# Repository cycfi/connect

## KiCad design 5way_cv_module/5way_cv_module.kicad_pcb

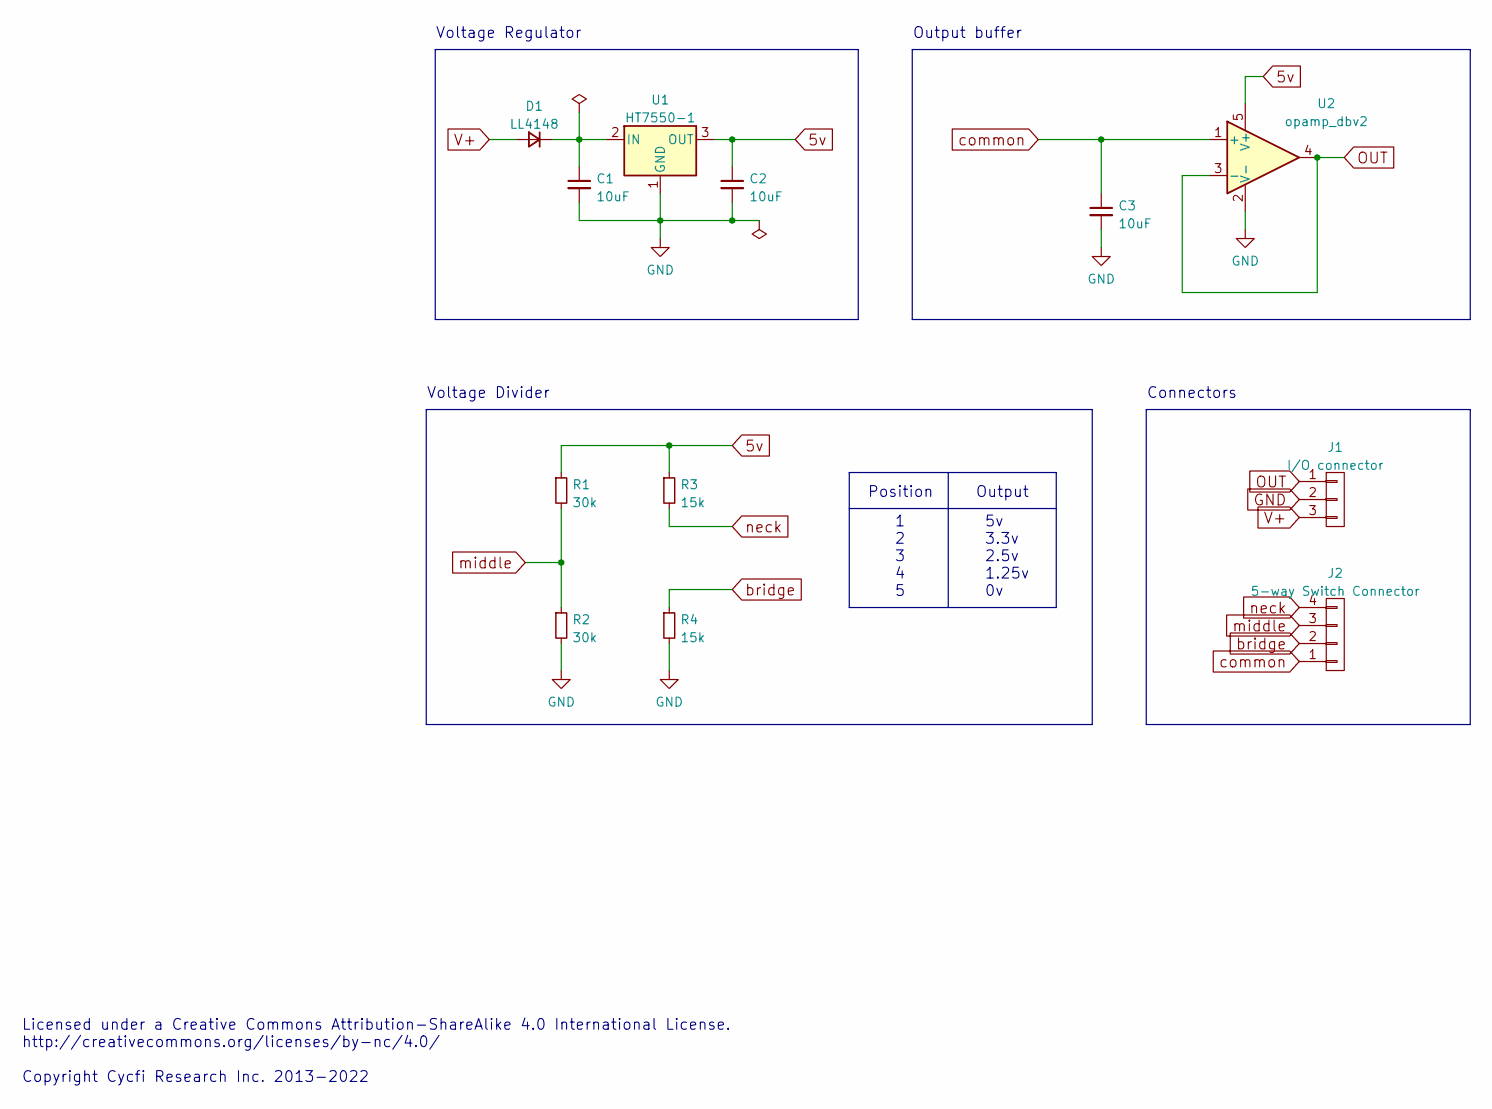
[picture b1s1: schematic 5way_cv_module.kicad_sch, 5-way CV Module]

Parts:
C1, C2, C3: 10uF; C_0603_1608Metric
D1: LL4148; D_MiniMELF
J1: I/O connector; pin_header_1x3p_2.54mm_smd_horizontal
J2: 5-way Switch Connector; pin_socket_1x4p_2.54mm_smd_horizontal
R1, R2: 30k; R_0402_1005Metric
R3, R4: 15k; R_0402_1005Metric
U1: HT7550-1; SOT-89-3
U2: opamp_dbv2; SOT-23-5

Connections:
5v: C2.1, R1.1, R3.1, U1.3 (OUT), U2.5 (V+)
GND: C1.2, C2.2, C3.2, J1.2, R2.2, R4.2, U1.1 (GND), U2.2 (V-)
unnamed: C1.1, D1.1 (K), U1.2 (IN)
OUT: J1.1, U2.3 (-), U2.4
V+: D1.2 (A), J1.3
bridge: J2.2, R4.1
common: C3.1, J2.1, U2.1 (+)
middle: J2.3, R1.2, R2.1
neck: J2.4, R3.2

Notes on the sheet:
Output
5v 3.3v 2.5v 1.25v 0v
Connectors
Voltage Divider
1 2 3 4 5
Licensed under a Creative Commons Attribution-ShareAlike 4.0 International License. http://creativecommons.org/licenses/by-nc/4.0/ Copyright Cycfi Research Inc. 2013-2022
Output buffer
Voltage Regulator
Position

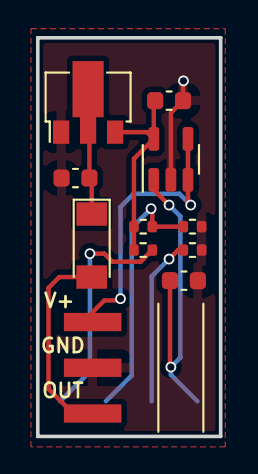
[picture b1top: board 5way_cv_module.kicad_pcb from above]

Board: 2 copper layers, 10.2 x 22.1 mm, 12 parts (1 on the bottom side), 9 nets.

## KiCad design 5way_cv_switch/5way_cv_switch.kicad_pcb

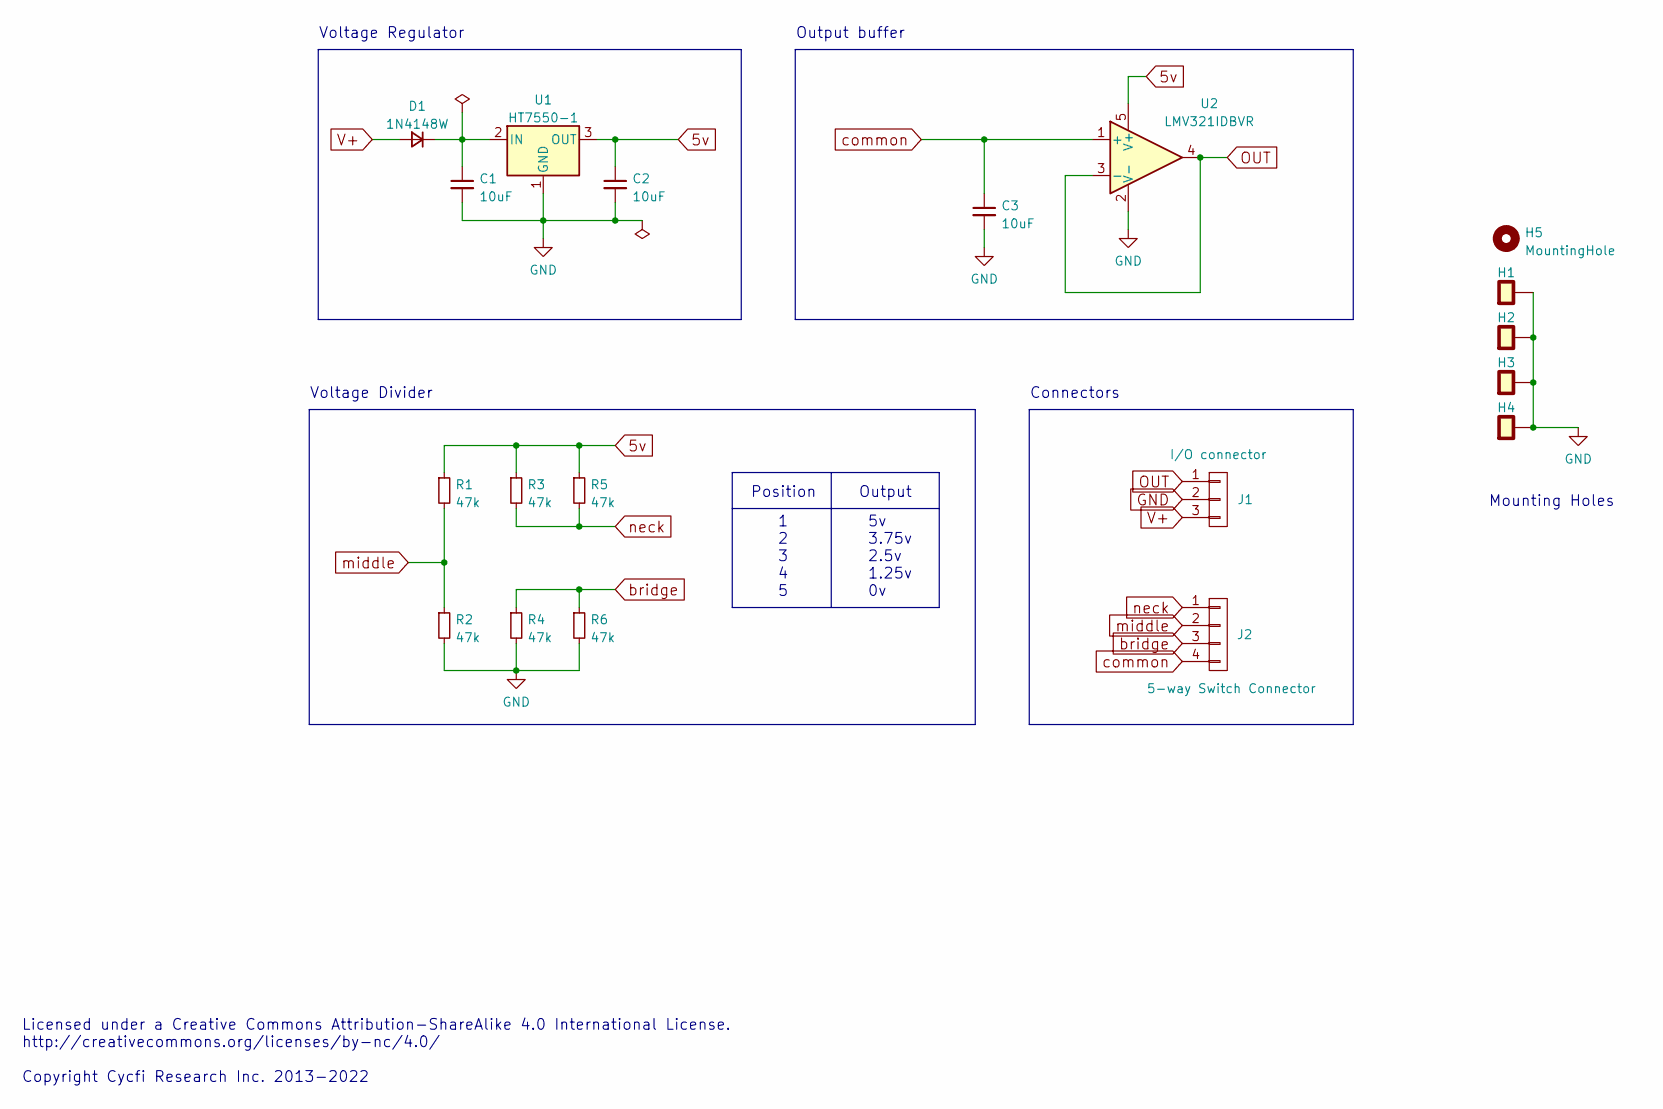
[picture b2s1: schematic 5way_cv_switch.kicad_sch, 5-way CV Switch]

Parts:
C1, C2, C3: 10uF; C_0805_2012Metric; LCSC C15850
D1: 1N4148W; D_SOD-123; LCSC C81598
H1, H2, H3, H4: single_pad; cond_hole_rect_1.2x3.5mm
H5: MountingHole; hole_2.65mm
J1: I/O connector; pin_header_1x3p_2.54mm_smd_horizontal
J2: 5-way Switch Connector; 5way_switch
R1, R2, R3, R4, R5, R6: 47k; R_0402_1005Metric; LCSC C25792
U1: HT7550-1; SOT-89-3; LCSC C16106
U2: LMV321IDBVR; SOT-23-5; LCSC C7972

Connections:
5v: C2.1, R1.1, R3.1, R5.1, U1.3 (OUT), U2.5 (V+)
GND: C1.2, C2.2, C3.2, H1.1, H2.1, H3.1, H4.1, J1.2, R2.2, R4.2, R6.2, U1.1 (GND), U2.2 (V-)
unnamed: C1.1, D1.1 (K), U1.2 (IN)
OUT: J1.1, U2.3 (-), U2.4
V+: D1.2 (A), J1.3
bridge: J2.3, R4.1, R6.1
common: C3.1, J2.4, U2.1 (+)
middle: J2.2, R1.2, R2.1
neck: J2.1, R3.2, R5.2

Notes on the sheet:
Output
5v 3.75v 2.5v 1.25v 0v
Connectors
Voltage Divider
1 2 3 4 5
Licensed under a Creative Commons Attribution-ShareAlike 4.0 International License. http://creativecommons.org/licenses/by-nc/4.0/ Copyright Cycfi Research Inc. 2013-2022
Output buffer
Voltage Regulator
Position
Mounting Holes

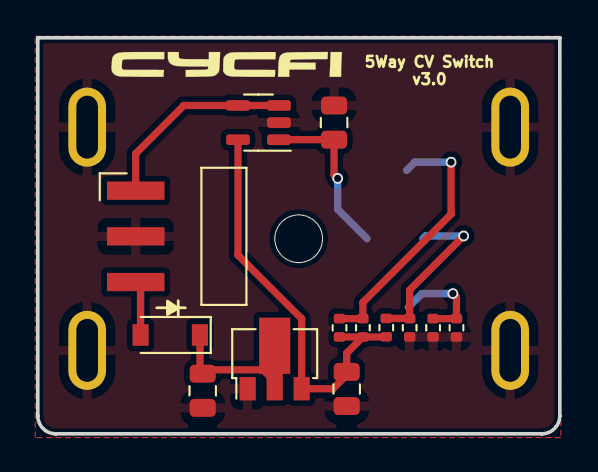
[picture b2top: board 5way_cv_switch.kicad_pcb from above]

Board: 2 copper layers, 29.0 x 22.0 mm, 19 parts (1 on the bottom side), 9 nets.

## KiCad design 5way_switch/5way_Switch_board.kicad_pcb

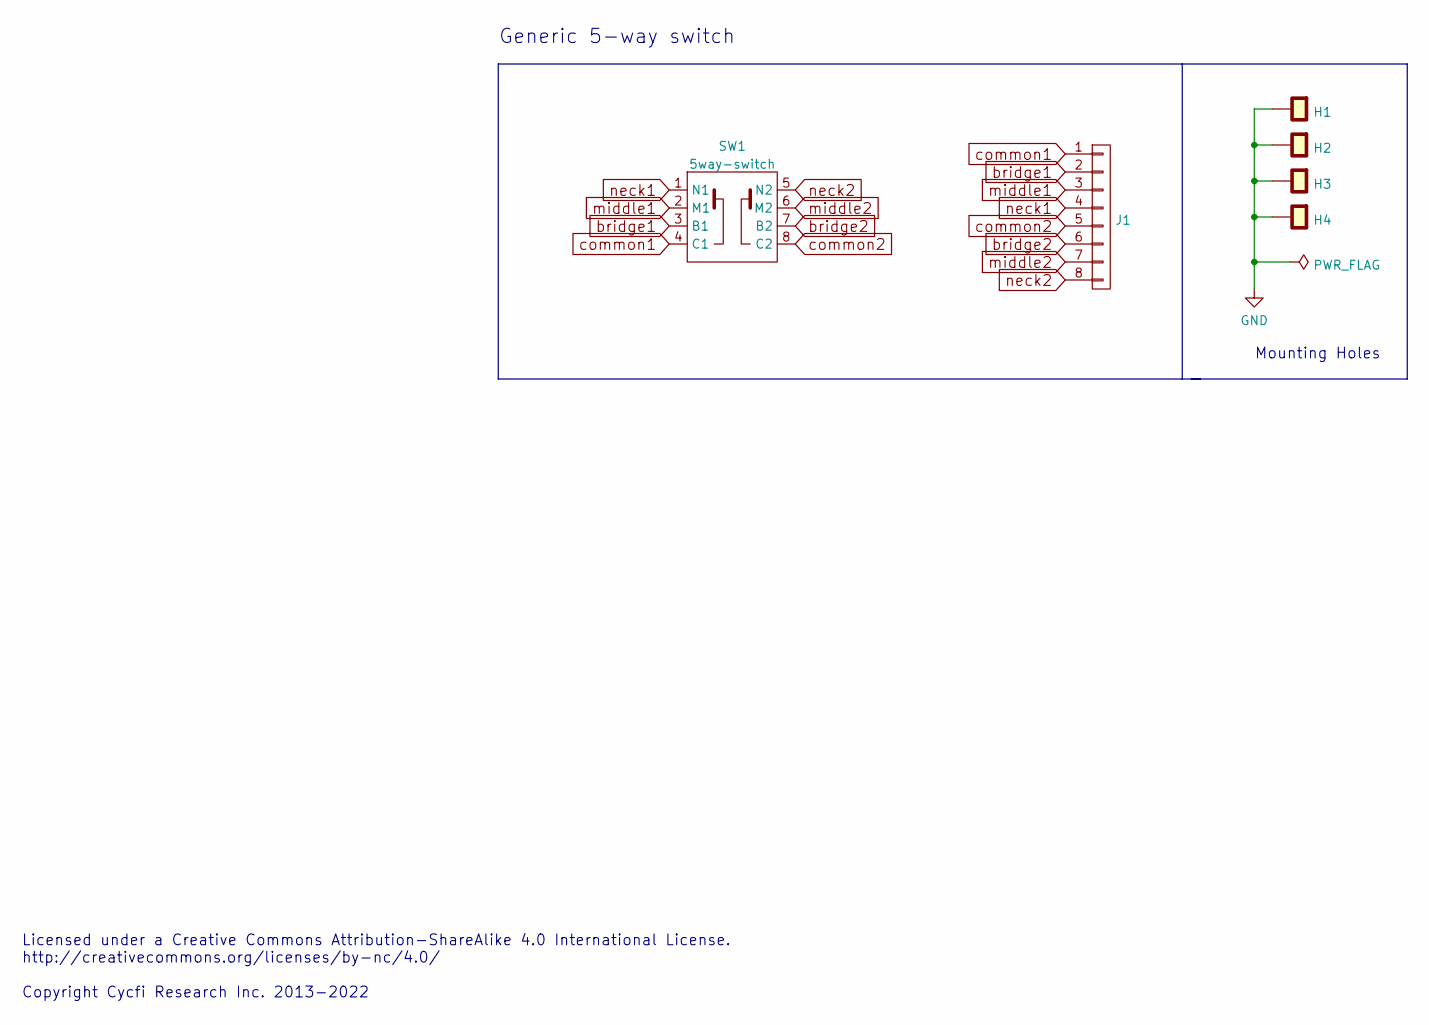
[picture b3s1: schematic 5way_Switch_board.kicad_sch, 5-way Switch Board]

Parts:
H1, H2, H3, H4: single_pad; cond_hole_rect_1.2x3.5mm
J1: CONN_01X8; pin_header_1x8p_2.54mm_smd_horizontal
SW1: 5way-switch; 5way_switch

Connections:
GND: H1.1, H2.1, H3.1, H4.1
bridge1: J1.2, SW1.3 (B1)
bridge2: J1.6, SW1.7 (B2)
common1: J1.1, SW1.4 (C1)
common2: J1.5, SW1.8 (C2)
middle1: J1.3, SW1.2 (M1)
middle2: J1.7, SW1.6 (M2)
neck1: J1.4, SW1.1 (N1)
neck2: J1.8, SW1.5 (N2)

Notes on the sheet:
Generic 5-way switch
Licensed under a Creative Commons Attribution-ShareAlike 4.0 International License. http://creativecommons.org/licenses/by-nc/4.0/ Copyright Cycfi Research Inc. 2013-2022
Mounting Holes

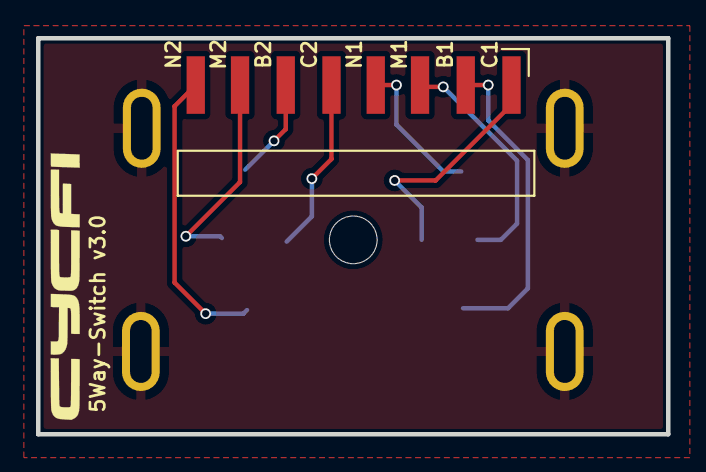
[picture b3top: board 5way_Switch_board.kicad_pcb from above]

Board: 2 copper layers, 35.0 x 22.0 mm, 6 parts (1 on the bottom side), 9 nets.

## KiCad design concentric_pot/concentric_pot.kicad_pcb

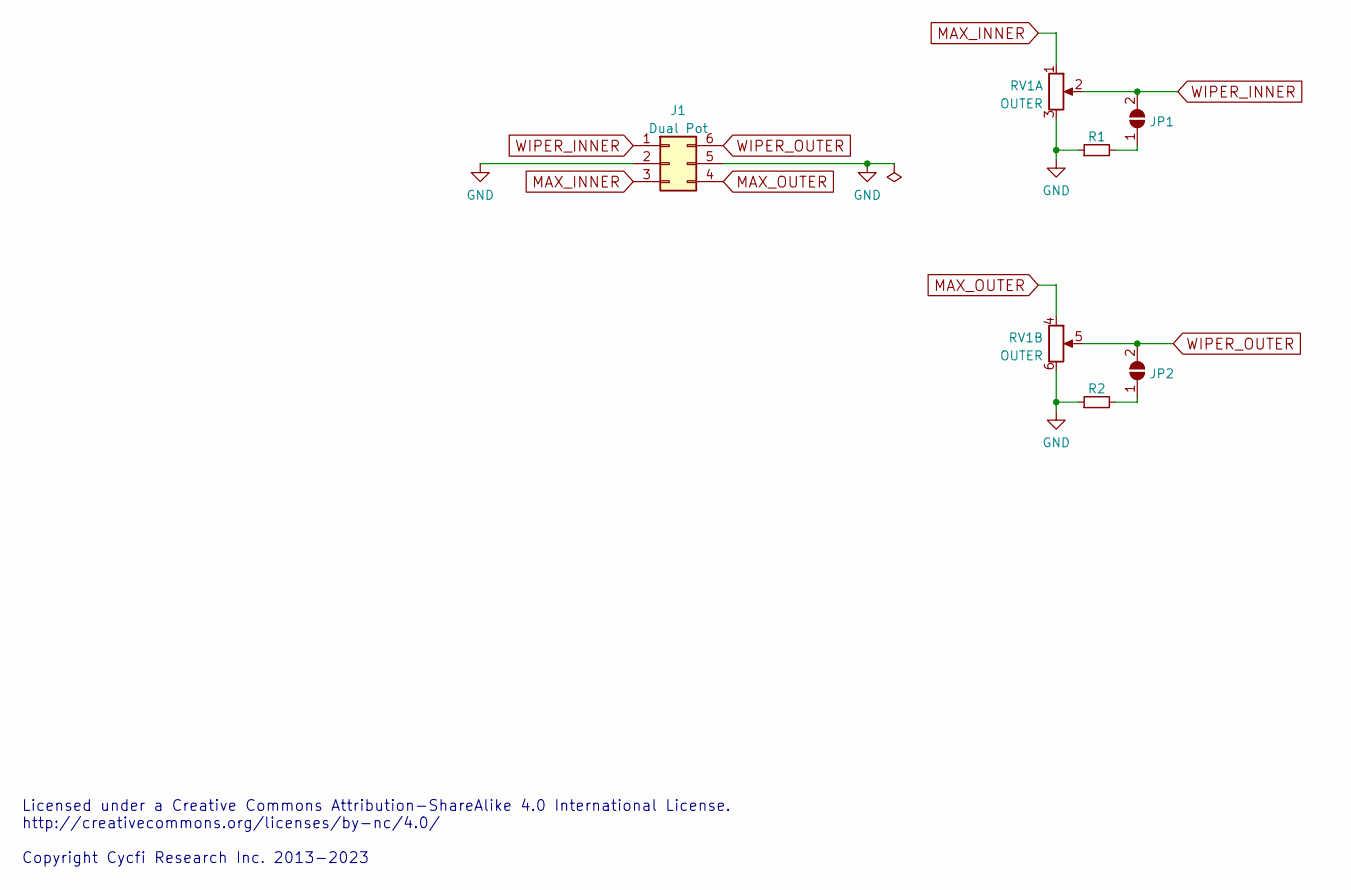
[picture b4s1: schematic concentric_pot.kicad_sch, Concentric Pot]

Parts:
J1: Dual Pot; pin_header_2x3p_2.54mm_smd_horizontal
JP1, JP2: SolderJumper_2_Open; SolderJumper-2_P1.3mm_Open_TrianglePad1.0x1.5mm
R1, R2: R_Small; R_0805_2012Metric_Pad1.20x1.40mm_HandSolder; LCSC C17673
RV1: OUTER; alpha_concentric_pot

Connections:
GND: J1.2, J1.5, R1.1, R2.1, RV1.3, RV1.6
MAX_INNER: J1.3, RV1.1
MAX_OUTER: J1.4, RV1.4
unnamed: JP1.1 (A), R1.2
unnamed: JP2.1 (A), R2.2
WIPER_INNER: J1.1, JP1.2 (B), RV1.2
WIPER_OUTER: J1.6, JP2.2 (B), RV1.5

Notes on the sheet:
Licensed under a Creative Commons Attribution-ShareAlike 4.0 International License. http://creativecommons.org/licenses/by-nc/4.0/ Copyright Cycfi Research Inc. 2013-2023

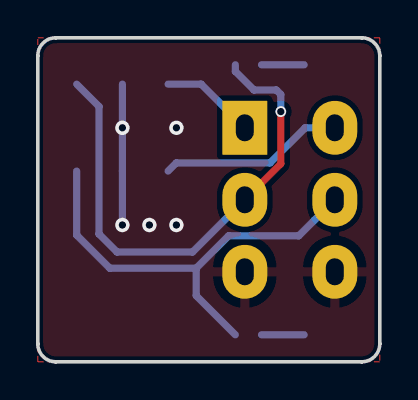
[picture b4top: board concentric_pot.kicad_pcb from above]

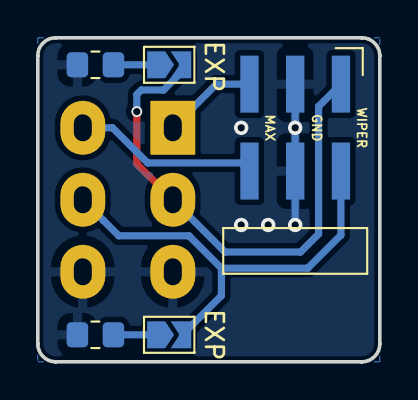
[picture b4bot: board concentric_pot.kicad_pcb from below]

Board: 2 copper layers, 19.0 x 18.0 mm, 6 parts (5 on the bottom side), 7 nets.

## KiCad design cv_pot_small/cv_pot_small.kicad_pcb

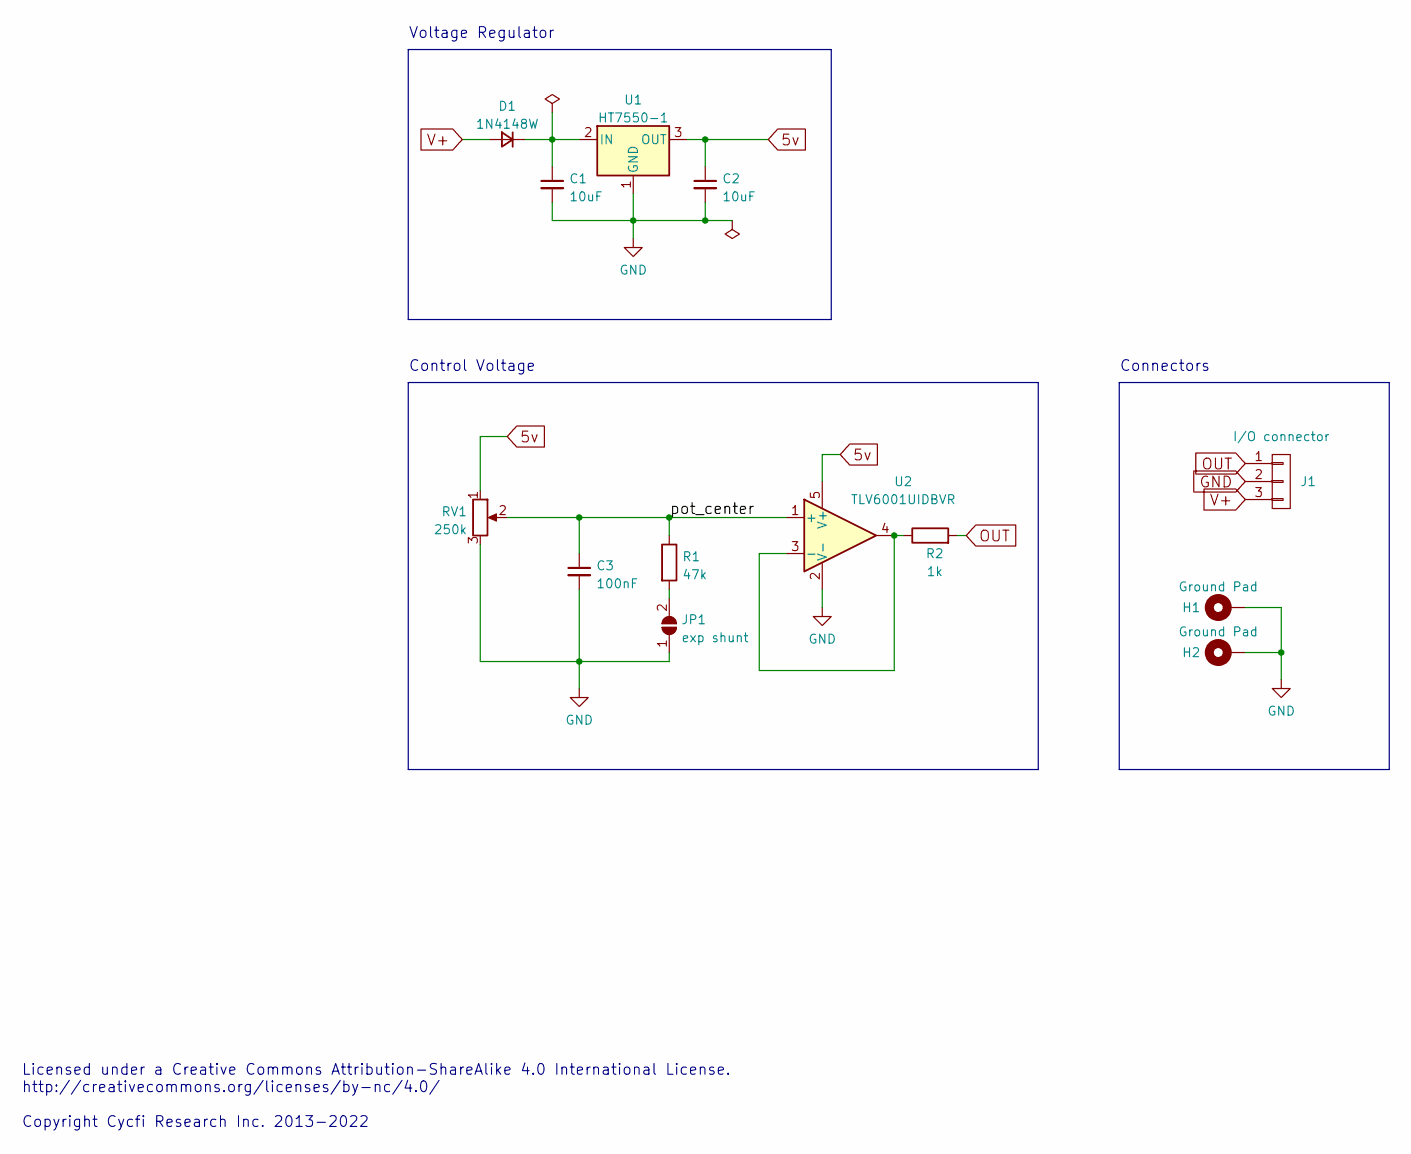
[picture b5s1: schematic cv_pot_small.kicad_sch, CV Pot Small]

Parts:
C1, C2: 10uF; C_0805_2012Metric; LCSC C15850
C3: 100nF; C_0402_1005Metric; LCSC C307331
D1: 1N4148W; D_SOD-123; LCSC C81598
H1, H2: Ground Pad; single-pad-2x2-circular
J1: I/O connector; pin_header_1x3p_2.54mm_smd_horizontal
JP1: exp shunt; SolderJumper-2_P1.3mm_Open_TrianglePad1.0x1.5mm
R1: 47k; R_0402_1005Metric; LCSC C25792
R2: 1k; R_0402_1005Metric; LCSC C11702
RV1: 250k; bourns_pdb181
U1: HT7550-1; SOT-89-3; LCSC C16106
U2: TLV6001UIDBVR; SOT-23-5; LCSC C544299

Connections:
5v: C2.1, RV1.1, U1.3 (OUT), U2.5 (V+)
/pot_center: C3.1, R1.1, RV1.2, U2.1 (+)
GND: C1.2, C2.2, C3.2, H1.1, H2.1, J1.2, JP1.1 (A), RV1.3, U1.1 (GND), U2.2 (V-)
unnamed: C1.1, D1.1 (K), U1.2 (IN)
unnamed: JP1.2 (B), R1.2
unnamed: R2.1, U2.3 (-), U2.4
OUT: J1.1, R2.2
V+: D1.2 (A), J1.3

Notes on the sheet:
Connectors
Licensed under a Creative Commons Attribution-ShareAlike 4.0 International License. http://creativecommons.org/licenses/by-nc/4.0/ Copyright Cycfi Research Inc. 2013-2022
Voltage Regulator
Control Voltage

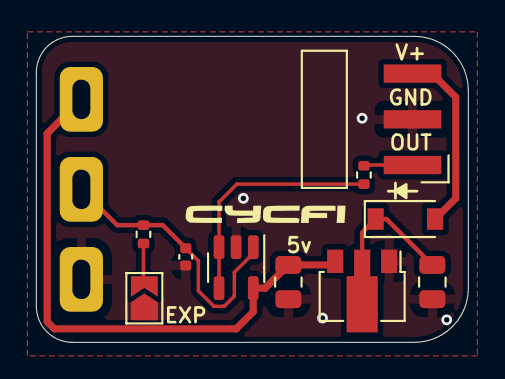
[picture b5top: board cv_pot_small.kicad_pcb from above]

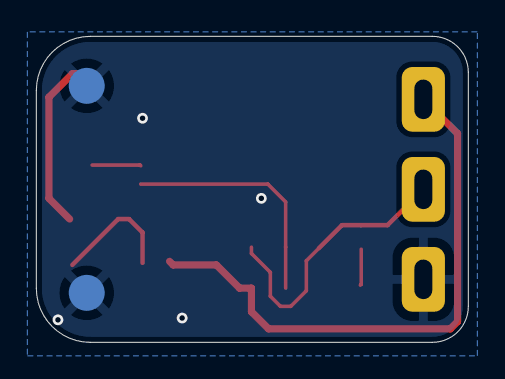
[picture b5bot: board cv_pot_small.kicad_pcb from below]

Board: 2 copper layers, 24.0 x 17.0 mm, 13 parts (2 on the bottom side), 8 nets.
